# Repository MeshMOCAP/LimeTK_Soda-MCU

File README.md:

# LimeVR_Soda_MCU

一个失败的小作品，但硬件本身还是有点价值的对吧

## 1.简介

LimeVR 的硬件基础，理想中会保持较低的价格还能有有足够有趣的功能和扩展\
由`ESP8684-WROOM-02C`模组提供算力，我也知道它的扩展性不太够了，但很便宜还有 BluetoothLE 支持，Soda 又不是烈酒

## 2.理想

Soda 应该只是 LimeVR 硬件设备中的一个，并且会作为其他设备和软件的底层设施，我为他塞上的一堆 jst PH 接口就足以说明问题了，但我的软件开发是在大部分硬件设计完后才开始的，我也完全没有注意到 esp32-c2 不算很强的扩展性，那些 GPIO 和大多数 arduino 的区别也不是那么那么多了。但还是那句话，它还是很便宜的对吧

LimeVR 因该会作为 SlimeVR 的一部分，保持可选的通用性但也应该弄一些原版不方便做的事情

> 我在写这段话之前从来没有把这两个名字放到一块看哈哈不是故意的啦。

取名叫 Lime 是因为其 青柠 的意思，我的名字叫 酸柠檬猹/SourLemonJuice 嘛

继续说扩展接口，我对这些接口的设想是能连接各种传感器从各种方面捕捉运动信息，但没有摄像头，没有usb，这些扩展能接的东西看来不算多了，或许哪天 Soda 会有自己的升级版本吧

我对追踪器和VR从接触以来一直都很感兴趣，我在 VRChat 游戏时长不到40小时的时候就去做了一套 SlimeVR 当然我不用啦，只是觉得它们很酷，但中间出了太多太多的问题，没有统一设计也就会这样\
就是这些原因导致了我现在想做一个新的追踪器方案，它的目标很长远，要搞好扩展性和高精度价格还不能特别特别贵，是有可能实现，但我实在不知道自己能不能完成，尤其是在软件上可能遇到的各种问题实在是头疼。

我不知道项目未来会变成什么样，那目前我想到的，想加进去的追踪方式只有

- 多机位红外摄像头
- 磁力传感器
- 特殊定位标志贴纸（甚至可以弄成衣服）

我也想用除了wifi以外的任何方式尝试连接追踪器，毕竟wifi的功耗和蓝牙差距还是很大的，更不用说有线连接什么的了

想法总是很多，但软件总是会在各个方面上阻碍你。\
好啦，接下来就继续希望这个项目能够真正变得可用吧

## 3.与现实

现实就是拿 ESP-IDF 写了好久的固件但发现什么都干不好，或许是我的 C 还不够强，又或许是官方文档写的差，我不是很想吧所有错全都赖给别人，但我到底错了多少呢\
无所谓了

总之，等 platformIO 支持 esp32-c2 了或许可以装上官方的固件吧
那样这些时间也不算是完全浪费
其实 c2 和 c3 的引脚什么的都是兼容的，倒是能基本直接换掉

整件事情也没那么无聊吧，至少让我找到了不少事情干，esp-idf
的文档要是写的更详细点，或许我现在也不会失去动力了吧
谁能想到所有技术栈里 freertos 和抄来的 kalmanFilter 都能弄好
最后被一个 i2c 和 spi 的驱动教训呢

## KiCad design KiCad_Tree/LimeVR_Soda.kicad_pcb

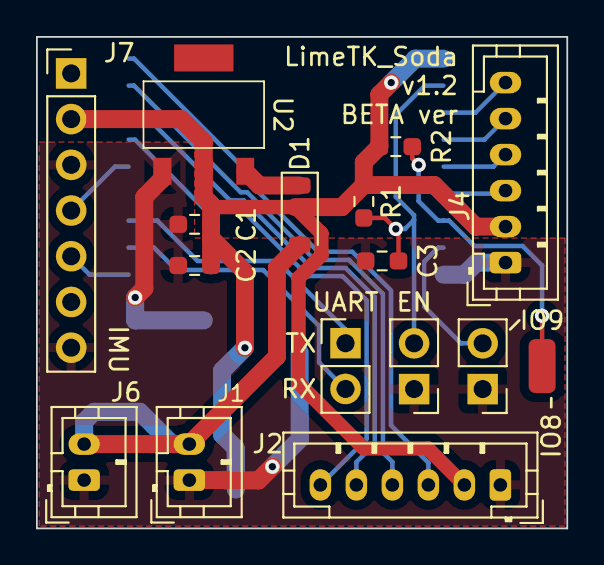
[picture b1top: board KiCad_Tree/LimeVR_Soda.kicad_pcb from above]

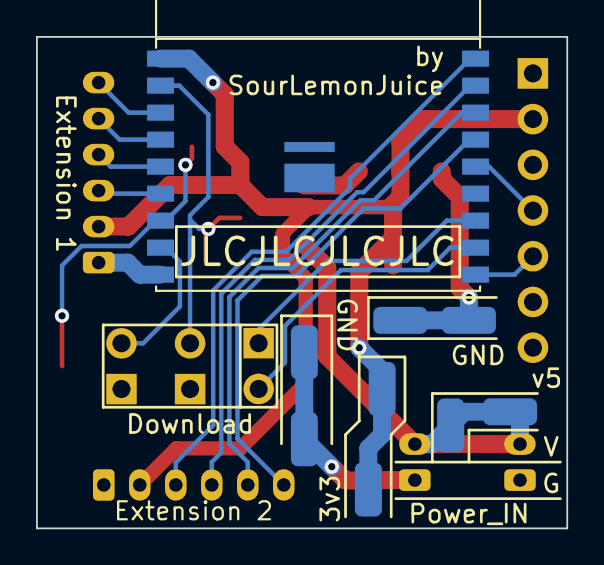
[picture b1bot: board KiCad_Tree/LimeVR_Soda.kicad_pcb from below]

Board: 2 copper layers, 29.5 x 27.3 mm, 25 parts (9 on the bottom side), 19 nets.

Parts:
C1, C2: 10uF/25V(20%); R_0603_1608Metric_Pad0.98x0.95mm_HandSolder
C3: 1uF/16V(10%); R_0603_1608Metric_Pad0.98x0.95mm_HandSolder
D1: 1N5817W; D_SOD-123
J1, J6: JST_PH-2p; JST_PH_B2B-PH-K_1x02_P2.00mm_Vertical
J2: Extension_Module_1_PH-6p; JST_PH_B6B-PH-K_1x06_P2.00mm_Vertical
J3: UART_Pinheader; PinHeader_1x02_P2.54mm_Vertical
J4: Extension_Module_2_PH-6p; JST_PH_B6B-PH-K_1x06_P2.00mm_Vertical
J5: Extension_3_pad; Wire_Pad_1.5x3
J7: IMU_BMI160_Module; PinHeader_1x07_P2.54mm_Vertical
J8: CHIP_PU_Pinheader; PinHeader_1x02_P2.54mm_Vertical
J9: GPIO9_Pinheader; PinHeader_1x02_P2.54mm_Vertical
J10, J11, J14, J16: GND Pad; Wire_Pad_1.5x3
J12, J13: V3.3 Pad; Wire_Pad_1.5x3
J15, J17: V5 Pad; Wire_Pad_1.5x3
R1: 10K(1%); R_0603_1608Metric_Pad0.98x0.95mm_HandSolder
R2: 10K(1%)(NC); R_0603_1608Metric_Pad0.98x0.95mm_HandSolder
U1: ESP8684-WROOM-02C
U2: SGM2212-3.3XKC3G.TR

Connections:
/Chip_PU: C3.1, J8.2, R1.2, U1.2 (EN/CHIP_PU)
/GIPO9: J9.2, U1.8 (GPIO9)
/U0RXD: J3.2, U1.11 (GPIO19/U0RXD)
/U0TXD: J3.1, U1.12 (GPIO20/U0TXD)
/VCC_3v3: C1.1, C2.1, J2.2, J4.2, J7.2, J12.1, J13.1, R1.1, R2.1, U1.1 (3V3), U2.2 (VOUT)
GND: C1.2, C2.2, C3.2, J1.1, J2.1, J4.1, J6.1, J7.3, J7.7, J8.1, J9.1, J10.1, J11.1, J14.1, J16.1, U1.9 (GND), U2.1 (GND)
unnamed: D1.2 (A), J1.2, J6.2, J15.1, J17.1
unnamed: D1.1 (K), U2.3 (VIN)
unnamed: J2.3, U1.18 (GPIO0/ADC1_CH0)
unnamed: J2.4, U1.17 (GPIO1/ADC1_CH1)
unnamed: J2.5, U1.16 (GPIO1/ADC1_CH2/FSPIQ)
unnamed: J2.6, U1.15 (GPIO3/ADC1_CH3)
unnamed: J4.3, U1.6 (GPIO7/FSPID/MTDO)
unnamed: J4.4, U1.5 (GPIO6/FSPICLK/MTCK)
unnamed: J4.5, U1.4 (GPIO5/FSPIWP/MTDI)
unnamed: J4.6, U1.3 (GPIO4/ADC1_CH4/FSPIHD/MTMS)
unnamed: J5.1, R2.2, U1.7 (GPIO8)
unnamed: J7.4, U1.14 (GPIO18)
unnamed: J7.5, U1.10 (GPIO10/FSPICS0)

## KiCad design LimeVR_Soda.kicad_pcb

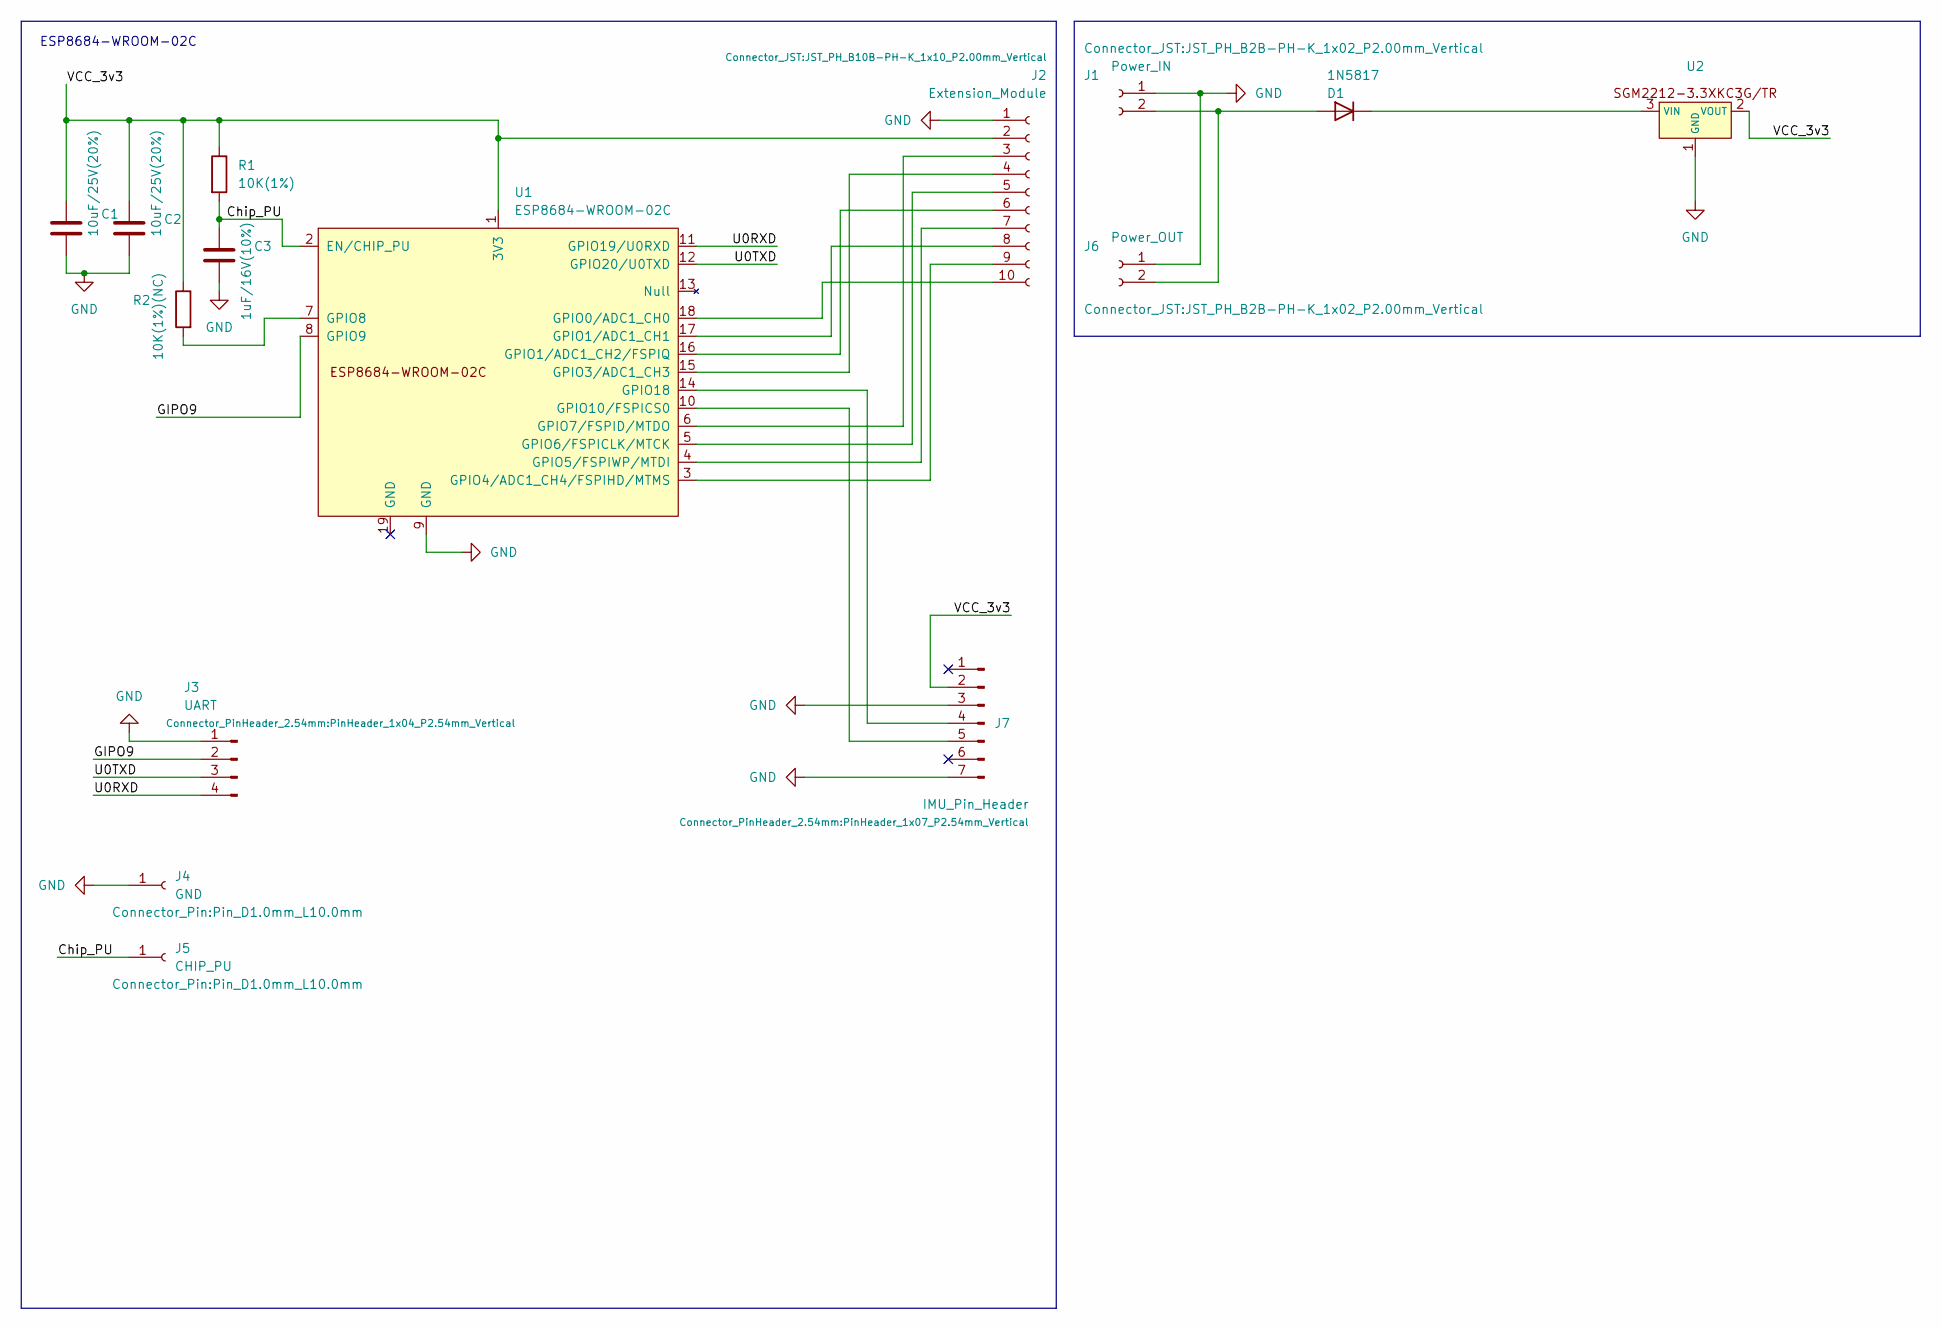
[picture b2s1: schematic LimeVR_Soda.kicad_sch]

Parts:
C1, C2: 10uF/25V(20%); R_1210_3225Metric_Pad1.30x2.65mm_HandSolder
C3: 1uF/16V(10%); R_1210_3225Metric_Pad1.30x2.65mm_HandSolder
D1: 1N5817; D_DO-41_SOD81_P7.62mm_Horizontal
J1: Power_IN; JST_PH_B2B-PH-K_1x02_P2.00mm_Vertical
J2: Extension_Module; JST_PH_B10B-PH-K_1x10_P2.00mm_Vertical
J3: UART; PinHeader_1x04_P2.54mm_Vertical
J4: GND; Pin_D1.0mm_L10.0mm
J5: CHIP_PU; Pin_D1.0mm_L10.0mm
J6: Power_OUT; JST_PH_B2B-PH-K_1x02_P2.00mm_Vertical
J7: IMU_Pin_Header; PinHeader_1x07_P2.54mm_Vertical
R1: 10K(1%); R_1210_3225Metric_Pad1.30x2.65mm_HandSolder
R2: 10K(1%)(NC); R_1210_3225Metric_Pad1.30x2.65mm_HandSolder
U1: ESP8684-WROOM-02C
U2: SGM2212-3.3XKC3G.TR

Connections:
/Chip_PU: C3.1, J5.1, R1.2, U1.2 (EN/CHIP_PU)
/GIPO9: J3.2, U1.8 (GPIO9)
/U0RXD: J3.4, U1.11 (GPIO19/U0RXD)
/U0TXD: J3.3, U1.12 (GPIO20/U0TXD)
/VCC_3v3: C1.1, C2.1, J2.2, J7.2, R1.1, R2.1, U1.1 (3V3), U2.2 (VOUT)
GND: C1.2, C2.2, C3.2, J1.1, J2.1, J3.1, J4.1, J6.1, J7.3, J7.7, U1.9 (GND), U2.1 (GND)
unnamed: D1.2 (A), J1.2, J6.2
unnamed: D1.1 (K), U2.3 (VIN)
unnamed: J2.3, U1.6 (GPIO7/FSPID/MTDO)
unnamed: J2.4, U1.15 (GPIO3/ADC1_CH3)
unnamed: J2.5, U1.5 (GPIO6/FSPICLK/MTCK)
unnamed: J2.6, U1.16 (GPIO1/ADC1_CH2/FSPIQ)
unnamed: J2.7, U1.4 (GPIO5/FSPIWP/MTDI)
unnamed: J2.8, U1.17 (GPIO1/ADC1_CH1)
unnamed: J2.9, U1.3 (GPIO4/ADC1_CH4/FSPIHD/MTMS)
unnamed: J2.10, U1.18 (GPIO0/ADC1_CH0)
unnamed: J7.4, U1.14 (GPIO18)
unnamed: J7.5, U1.10 (GPIO10/FSPICS0)
unnamed: R2.2, U1.7 (GPIO8)

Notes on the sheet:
ESP8684-WROOM-02C

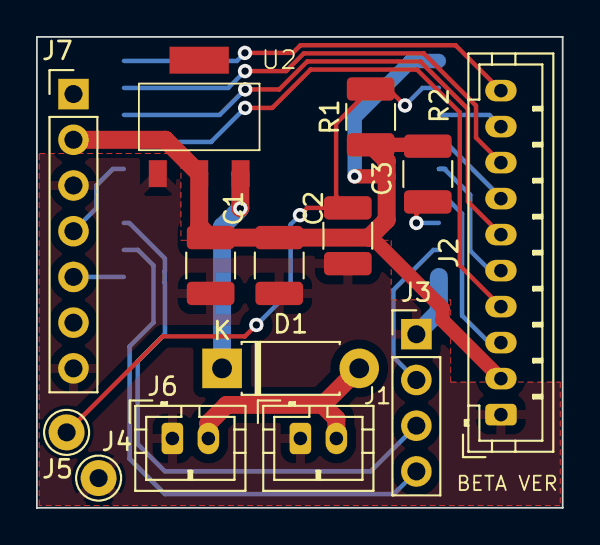
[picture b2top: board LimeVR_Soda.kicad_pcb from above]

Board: 2 copper layers, 29.2 x 26.2 mm, 15 parts (1 on the bottom side), 19 nets.

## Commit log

2024-03-03 初次提交
2024-03-06 kicad项目文件移到单独文件夹
2024-03-06 完善.gitignore
2024-03-12 v1.2 一个无聊又可悲的版本
    我恨 esp-idf
    总之，等 platformIO 支持 esp32-c2 了或许可以装上官方的固件吧
    那样这些时间也不算是完全浪费
    又或许 c2 和 c3 的引脚什么的都是兼容的，倒是能基本直接换掉
    无聊
    但也没那么无聊吧，至少让我找到了不少事情干，espidf
2024-03-13 添加自述文件
2024-03-13 添加 unlicense
2024-03-13 更新 .gitignore
